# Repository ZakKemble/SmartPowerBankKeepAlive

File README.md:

# Smart Power Bank Keep-Alive (v2.x)

Keep USB power banks alive when powering low-power projects with this pulsed constant current sink USB module.

[https://blog.zakkemble.net/smart-power-bank-keep-alive/](https://blog.zakkemble.net/smart-power-bank-keep-alive/)

|Hardware version|Branch|Photo|
|---|---|---|
|v2.x|[main](https://github.com/zakkemble/SmartPowerBankKeepAlive) (you are currently on this one)||
|v1.x|[v1.x](https://github.com/zakkemble/SmartPowerBankKeepAlive/tree/v1.x)||

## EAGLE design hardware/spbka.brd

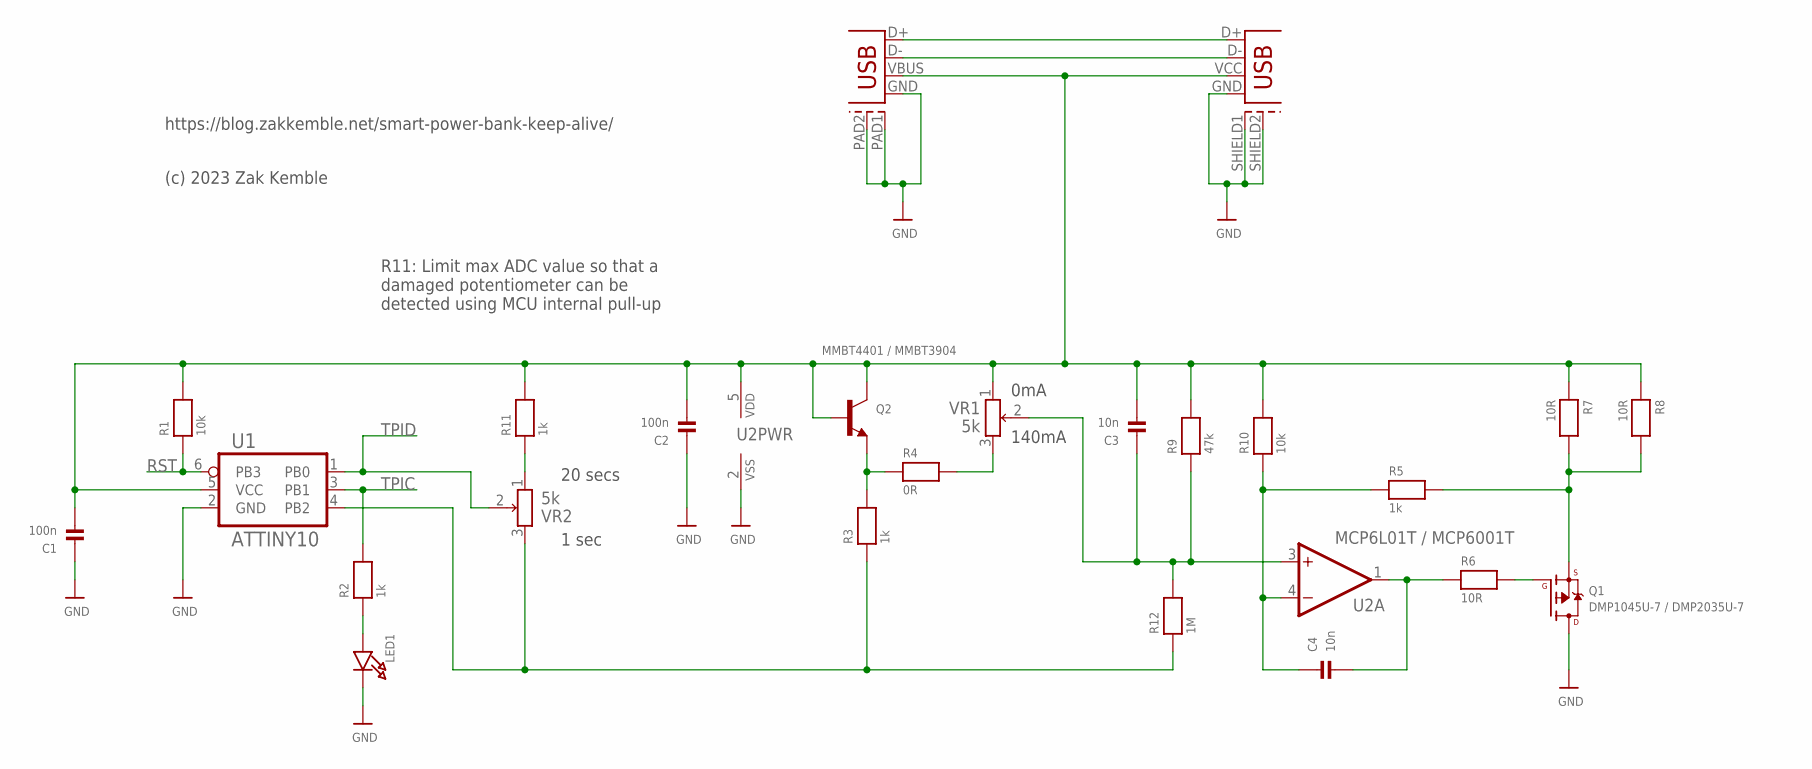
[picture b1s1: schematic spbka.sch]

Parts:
C1, C2: 100n; 0402_XSMALL
C3, C4: 10n; 0402_XSMALL
LED1: LED0603_NOOUTLINE; CHIPLED_0603_NOOUTLINE
Q1: DMP1045U-7 / DMP2035U-7; SOT-23-WIDE
Q2: MMBT4401 / MMBT3904; SOT23-R
R1, R10: 10k; 0402_XSMALL
R2, R3, R5, R11: 1k; 0402_XSMALL
R4: 0R; 0402_XSMALL
R6, R7, R8: 10R; 0402_XSMALL
R9: 47k; 0402_XSMALL
R12: 1M; 0402_XSMALL
U1: ATTINY10; SOT23-6_SM_PAD
U2: MCP6L01T / MCP6001T; SOT23-5_SM_PAD
USB1: USB-TYPE-AHORZ; USB-TYPE-A
USB2: USB-PLUG; USB-TYPE-A-PLUG-SLOT
VR1, VR2: 5k; TRIMPOT_BOURNS3MM

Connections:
GND: C1.1, C2.1, LED1.C, Q1.3 (D), U1.2 (GND), U2.2 (VSS), USB1.GND, USB1.SHIELD1 (SHEILD1), USB1.SHIELD2 (SHEILD2), USB2.GND, USB2.PAD1 (SHEILD1), USB2.PAD2 (SHEILD2)
unnamed: Q2.2 (E), R3.2, R4.1
unnamed: Q1.2 (S), R5.2, R7.2, R8.2
unnamed: C4.2, R6.1, U2.1 (OUT)
unnamed: LED1.A, R2.1
unnamed: USB1.D+, USB2.D+
unnamed: USB1.D-, USB2.D-
unnamed: R3.1, R12.1, U1.4 (PB2), VR2.3 (1E)
unnamed: C4.1, R5.1, R10.1, U2.4 (-IN)
unnamed: R4.2, VR1.3 (1E)
unnamed: Q1.1 (G), R6.2
unnamed: C3.1, R9.1, R12.2, U2.3 (+IN), VR1.2 (1S)
unnamed: R11.1, VR2.1 (1A)
RST: R1.1, U1.6 (PB3)
TPIC: R2.2, U1.3 (PB1)
TPID: U1.1 (PB0), VR2.2 (1S)
VBUS: C1.2, C2.2, C3.2, Q2.1 (B), Q2.3 (C), R1.2, R7.1, R8.1, R9.2, R10.2, R11.2, U1.5 (VCC), U2.5 (VDD), USB1.VCC (VBUS), USB2.VBUS, VR1.1 (1A)

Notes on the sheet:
0mA
140mA
https://blog.zakkemble.net/smart-power-bank-keep-alive/
(c) 2023 Zak Kemble
20 secs
1 sec
R11: Limit max ADC value so that a damaged potentiometer can be detected using MCU internal pull-up

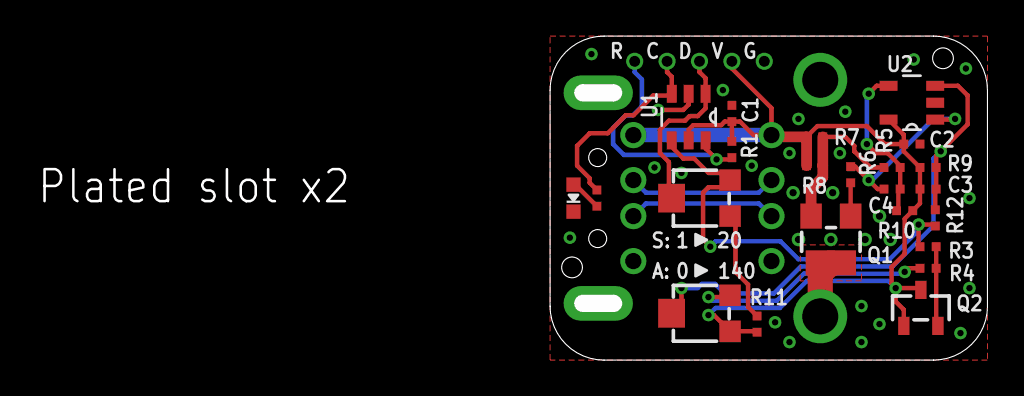
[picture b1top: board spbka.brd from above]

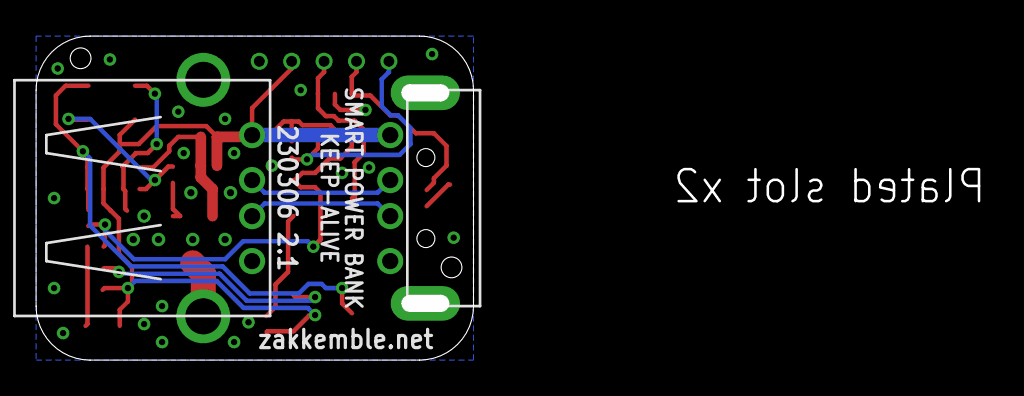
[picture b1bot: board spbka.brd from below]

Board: 2 copper layers, 52.0 x 17.1 mm, 25 parts (2 on the bottom side), 17 nets.

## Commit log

2020-02-10 Initial commit :sweat_drops:
2020-03-26 Add images for wiki
2020-03-26 Another wiki image
2020-03-26 Pass variables to makefile
2020-05-16 Some small changes, HW v1.2
    Hardware bumped to v1.2:
    Added unmasked vias for VCC and GND to make it easier to program.
    Made USB3 socket pads longer (some components and things had to be moved slightly for this).
2024-06-30 hardware v2.1
2024-06-30 firmware v2.x
2024-06-30 update images

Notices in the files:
parts and their libraries:
microbuilder: This work is placed in the public domain, and may be freely used for commercial and non-commercial work with the following conditions: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
